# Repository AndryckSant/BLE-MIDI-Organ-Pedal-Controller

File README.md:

# BLE MIDI Organ Pedal Controller

Firmware for an ESP32-based expression-pedal controller that sends MIDI Control Change messages over BLE MIDI. The firmware is organized into application, FSM, service, model, and driver layers.

Firmware version: **1.2.0**

## Features

- BLE MIDI output for two expression pedals and up to eight physical buttons.
- ADS1115 input sampling, pedal smoothing, calibration, normalization, and MIDI mapping.
- Per-pedal adaptive auto-range or manually configured calibration limits.
- Configurable button input polarity and momentary or latch MIDI behavior.
- OLED status display and a Wi-Fi access-point configuration portal.
- System configuration persisted in ESP32 non-volatile storage (NVS), including migration from earlier configuration formats.

## Hardware

- ESP32 with BLE support.
- ADS1115 I2C analog-to-digital converter (default address `0x48`).
- SSD1306 I2C OLED display (default address `0x3C`).
- Up to two expression pedals and eight MIDI buttons.

### Default pin assignments

| Function | ESP32 pin / input |
| --- | --- |
| I2C SDA | GPIO 21 |
| I2C SCL | GPIO 22 |
| Configuration button | GPIO 15 |
| Status LED | GPIO 2 |
| MIDI buttons 1-8 | GPIO 13, 12, 14, 27, 26, 25, 33, 32 |
| Pedal inputs | ADS1115 channels A0 and A1 by default |

Connect the buttons with external pull-down resistors. The dedicated configuration button is also read as a digital input. Connect each pedal output to its assigned ADS1115 input and share ground; use a supply voltage appropriate for the pedal and board.

## Configuration portal

Enter configuration mode by pressing the button on GPIO 15 or sending `c`/`C` through Serial at **115200 baud**. BLE MIDI is stopped while the portal is active.

The ESP32 starts an open Wi-Fi access point named **BLE MIDI Controller Setup**. Connect to it and open the IP address shown on the OLED and in the Serial output. The portal lets you configure:

- Each pedal's enabled state, ADS1115 channel, MIDI channel, MIDI CC, calibration minimum/maximum, and auto-range setting.
- Each button's enabled state, GPIO, input polarity, MIDI channel, MIDI CC, and behavior.
- MIDI channels from 1 to 16 and Control Change numbers from 0 to 127.

Button behavior:

- **Momentary:** sends value 127 when pressed and 0 when released.
- **Latch:** alternates between 127 and 0 on successive presses; release sends nothing. This is the default.

Each button input has a 40 ms debounce interval. Use the assigned MIDI-button GPIOs (13, 12, 14, 27, 26, 25, 33, or 32); GPIO 15 is reserved for configuration mode.

Saving settings or restoring factory defaults persists the configuration to NVS and restarts the device. Sending `x`/`X` exits the portal without saving and returns to normal BLE MIDI operation. If the access point cannot start, the OLED displays an error for five seconds before the device restarts.

Factory defaults enable both pedals on ADS1115 channels A0 and A1, MIDI channel 1, with CC 11 and CC 7 respectively. Adaptive auto-range is enabled. All eight buttons default to disabled, use the GPIO assignments above, and have MIDI channel 1, CCs 20-27, and latch behavior.

## Pedal calibration

Auto-range is enabled by default and adapts the calibration range as new pedal extremes are detected. Disable auto-range to use fixed minimum and maximum values configured in the portal. For a useful fixed calibration, set the minimum below the maximum and exercise the pedal across its intended range.

## Build and upload

1. Install the ESP32 board support and the Arduino libraries required by the source, including Adafruit ADS1X15, Adafruit GFX, Adafruit SSD1306, and the BLE MIDI library.
2. Open `Firmware/main/main.ino` in the Arduino IDE, select the target ESP32 board and port, then compile and upload.
3. Open Serial Monitor at **115200 baud** for startup messages and configuration-mode IP details.
4. Pair the BLE MIDI device named **BLE MIDI Controller** with the host and connect to receive MIDI CC messages.

The web-page source is `Firmware/main/src/core/states/config_page.html`; its firmware-embedded header is `Firmware/main/src/core/states/config_page.h`. After editing the HTML, regenerate the header by running `.\Firmware\tools\embed_config_page.ps1` from the repository root.

## Architecture

- `Firmware/main/main.ino` — Arduino `setup()`/`loop()` wrapper.
- `Firmware/main/src/app/` — application initialization, coordination, and runtime processing.
- `Firmware/main/src/core/` — FSM, event queue, and application states, including BLE, streaming, and configuration.
- `Firmware/main/src/drivers/` — ADS1115, BLE, OLED, and NVS hardware access.
- `Firmware/main/src/models/` — pedal, button, calibration, MIDI, and system configuration data.
- `Firmware/main/src/services/` — configuration persistence, input processing, calibration, display, and MIDI services.
- `Firmware/tools/` — utility for embedding the configuration page in the firmware.
- `Hardware/` — KiCad board design and related hardware files.
- `Docs/` — architecture and configuration-portal notes.

## License

- Firmware and original software in `Firmware/` are licensed under the [MIT License](Firmware/LICENSE).
- Hardware design files in `Hardware/` are licensed under [CERN-OHL-S-2.0](Hardware/LICENSE) (Strongly Reciprocal).
- These licenses apply to the original project work in their respective directories. Third-party libraries and other third-party materials remain under their own licenses; see their respective sources for terms.

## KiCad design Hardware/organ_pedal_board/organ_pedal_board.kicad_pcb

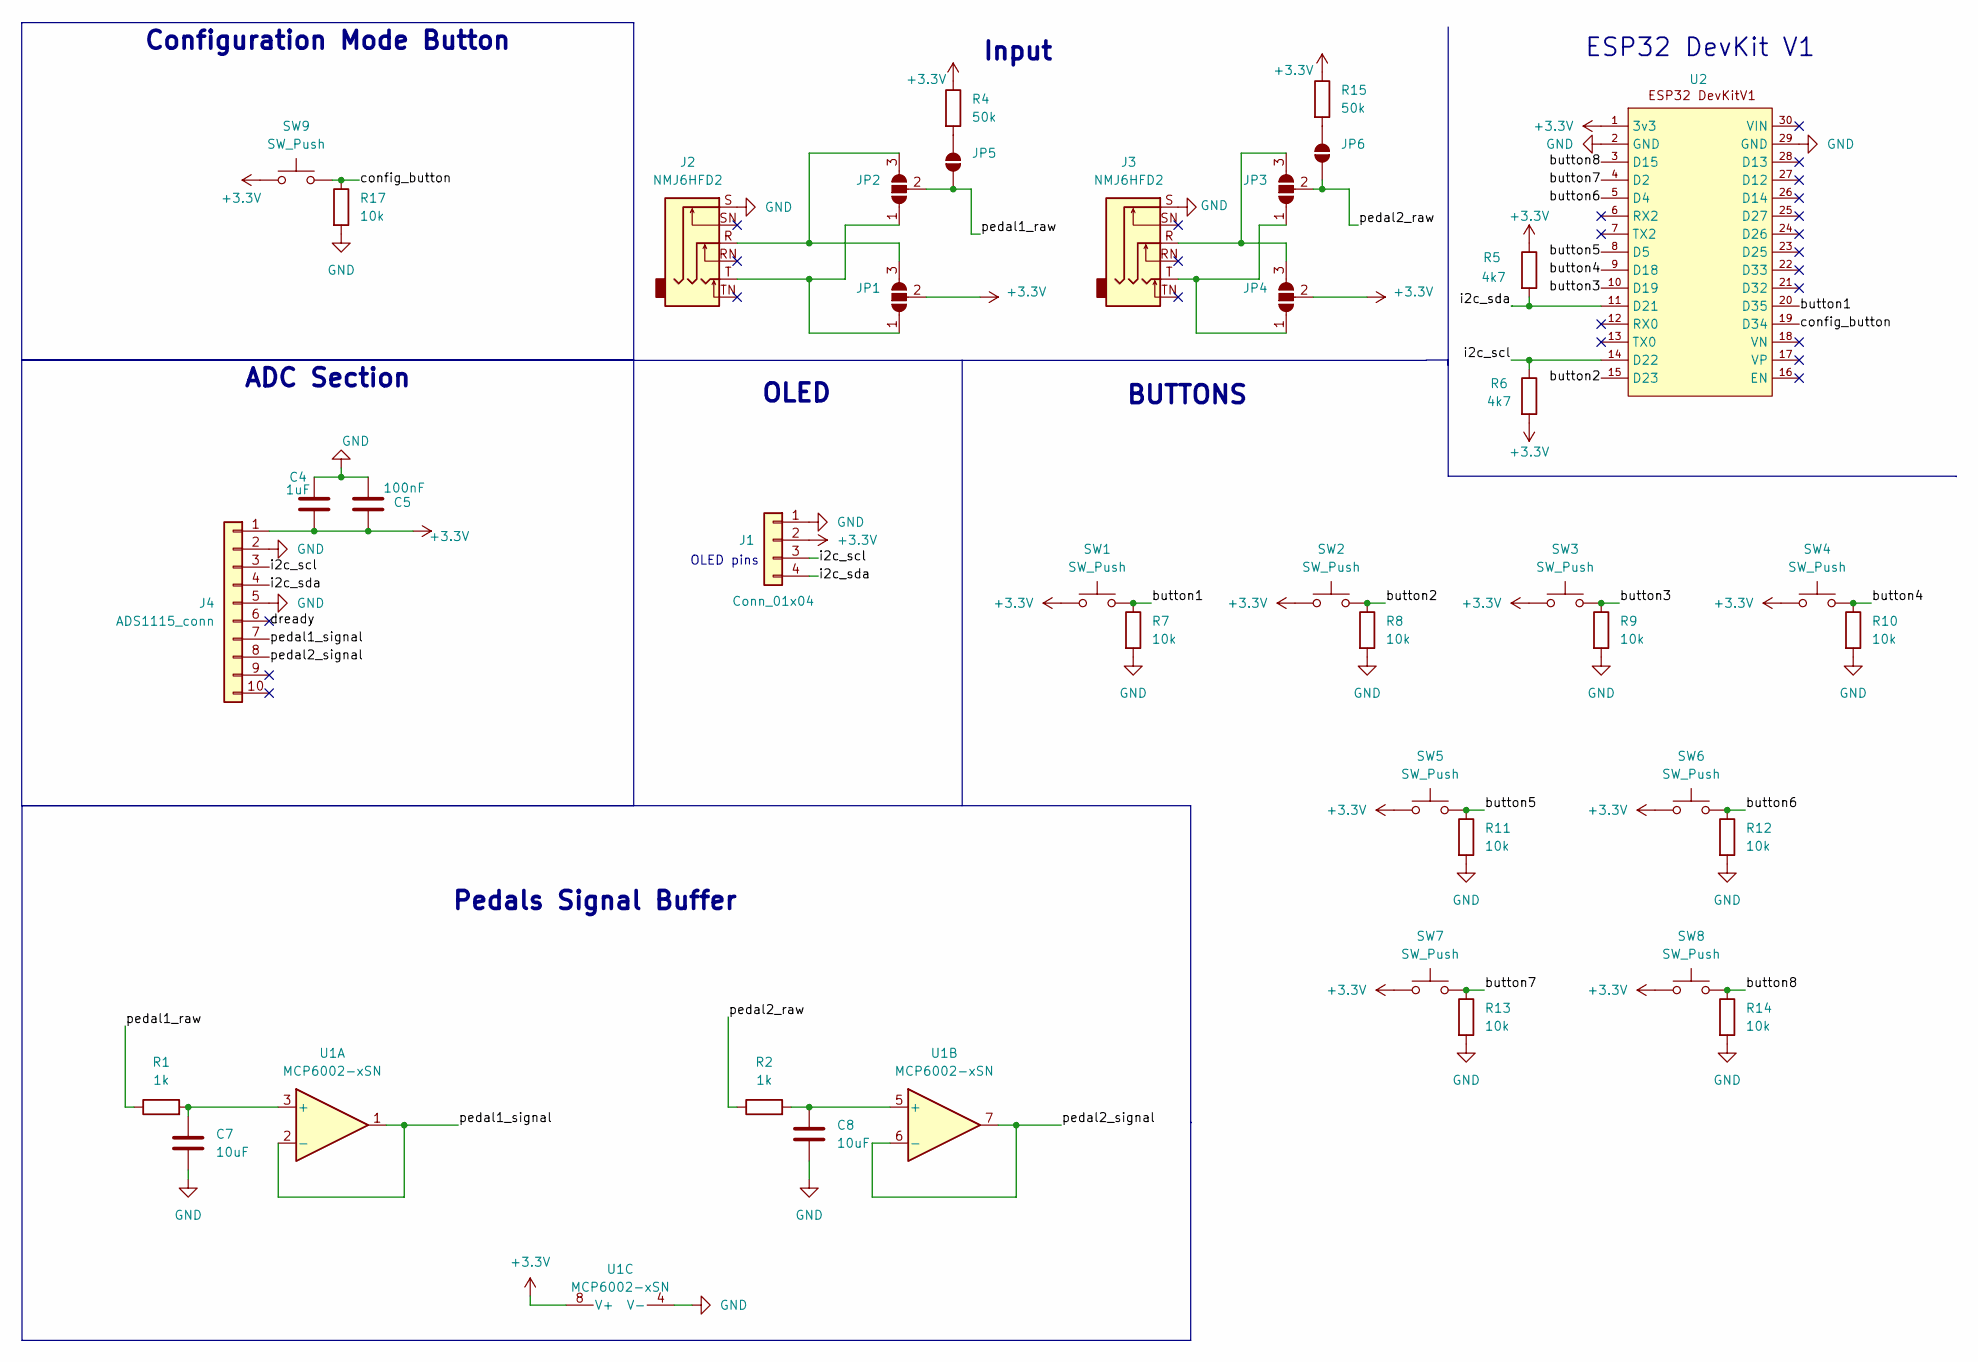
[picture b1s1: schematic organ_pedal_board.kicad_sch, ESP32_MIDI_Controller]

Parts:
C4: 1uF; C_Disc_D3.0mm_W1.6mm_P2.50mm
C5: 100nF; C_Disc_D3.0mm_W1.6mm_P2.50mm
C7, C8: 10uF; C_Disc_D3.0mm_W1.6mm_P2.50mm
J1: Conn_01x04; PinSocket_1x04_P2.54mm_Vertical
J2, J3: NMJ6HFD2; Jack_6.35mm_Neutrik_NMJ6HFD2_Horizontal
J4: ADS1115_conn; PinSocket_1x10_P2.54mm_Vertical
JP1, JP2, JP3, JP4: SolderJumper_3_Open; SolderJumper-3_P1.3mm_Open_RoundedPad1.0x1.5mm
JP5, JP6: SolderJumper_2_Open; SolderJumper-2_P1.3mm_Open_RoundedPad1.0x1.5mm
R1, R2: 1k; R_Axial_DIN0204_L3.6mm_D1.6mm_P1.90mm_Vertical
R4, R15: 50k; R_Axial_DIN0204_L3.6mm_D1.6mm_P1.90mm_Vertical
R5, R6: 4k7; R_Axial_DIN0204_L3.6mm_D1.6mm_P1.90mm_Vertical
R7, R8, R9, R10, R11, R12, R13, R14, R17: 10k; R_Axial_DIN0204_L3.6mm_D1.6mm_P1.90mm_Vertical
SW1, SW2, SW3, SW4, SW5, SW6, SW7, SW8: SW_Push; JST_XH_S2B-XH-A-1_1x02_P2.50mm_Horizontal
SW9: SW_Push; SW_PUSH_6mm
U1: MCP6002-xSN; SOIC-8_3.9x4.9mm_P1.27mm
U2: esp32_devkit_v1_doit

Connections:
+3.3V: C4.2, C5.1, J1.2, J4.1, JP1.2 (C), JP4.2 (C), R4.1, R5.1, R6.2, R15.1, SW1.1, SW2.1, SW3.1, SW4.1, SW5.1, SW6.1, SW7.1, SW8.1, SW9.1, U1.8 (V+), U2.1 (3v3)
/button1: R7.1, SW1.2, U2.20 (D35)
/button2: R8.1, SW2.2, U2.15 (D23)
/button3: R9.1, SW3.2, U2.10 (D19)
/button4: R10.1, SW4.2, U2.9 (D18)
/button5: R11.1, SW5.2, U2.8 (D5)
/button6: R12.1, SW6.2, U2.5 (D4)
/button7: R13.1, SW7.2, U2.4 (D2)
/button8: R14.1, SW8.2, U2.3 (D15)
/config_button: R17.1, SW9.2, U2.19 (D34)
/dready: J4.6
/i2c_scl: J1.3, J4.3, R6.1, U2.14 (D22)
/i2c_sda: J1.4, J4.4, R5.2, U2.11 (D21)
/pedal1_raw: JP2.2 (C), JP5.1 (A), R1.1
/pedal1_signal: J4.7, U1.1, U1.2 (-)
/pedal2_raw: JP3.2 (C), JP6.1 (A), R2.1
/pedal2_signal: J4.8, U1.6 (-), U1.7
GND: C4.1, C5.2, C7.2, C8.2, J1.1, J2.S, J3.S, J4.2, J4.5, R7.2, R8.2, R9.2, R10.2, R11.2, R12.2, R13.2, R14.2, R17.2, U1.4 (V-), U2.2 (GND), U2.29 (GND)
unnamed: J2.T, JP1.1 (A), JP2.1 (A)
unnamed: J2.R, JP1.3 (B), JP2.3 (B)
unnamed: J3.T, JP3.1 (A), JP4.1 (A)
unnamed: J3.R, JP3.3 (B), JP4.3 (B)
unnamed: JP5.2 (B), R4.2
unnamed: JP6.2 (B), R15.2
unnamed: C7.1, R1.2, U1.3 (+)
unnamed: C8.1, R2.2, U1.5 (+)

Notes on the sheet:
ESP32 DevKit V1
BUTTONS
Input
OLED
Pedals Signal Buffer
OLED pins
ADC Section
Configuration Mode Button

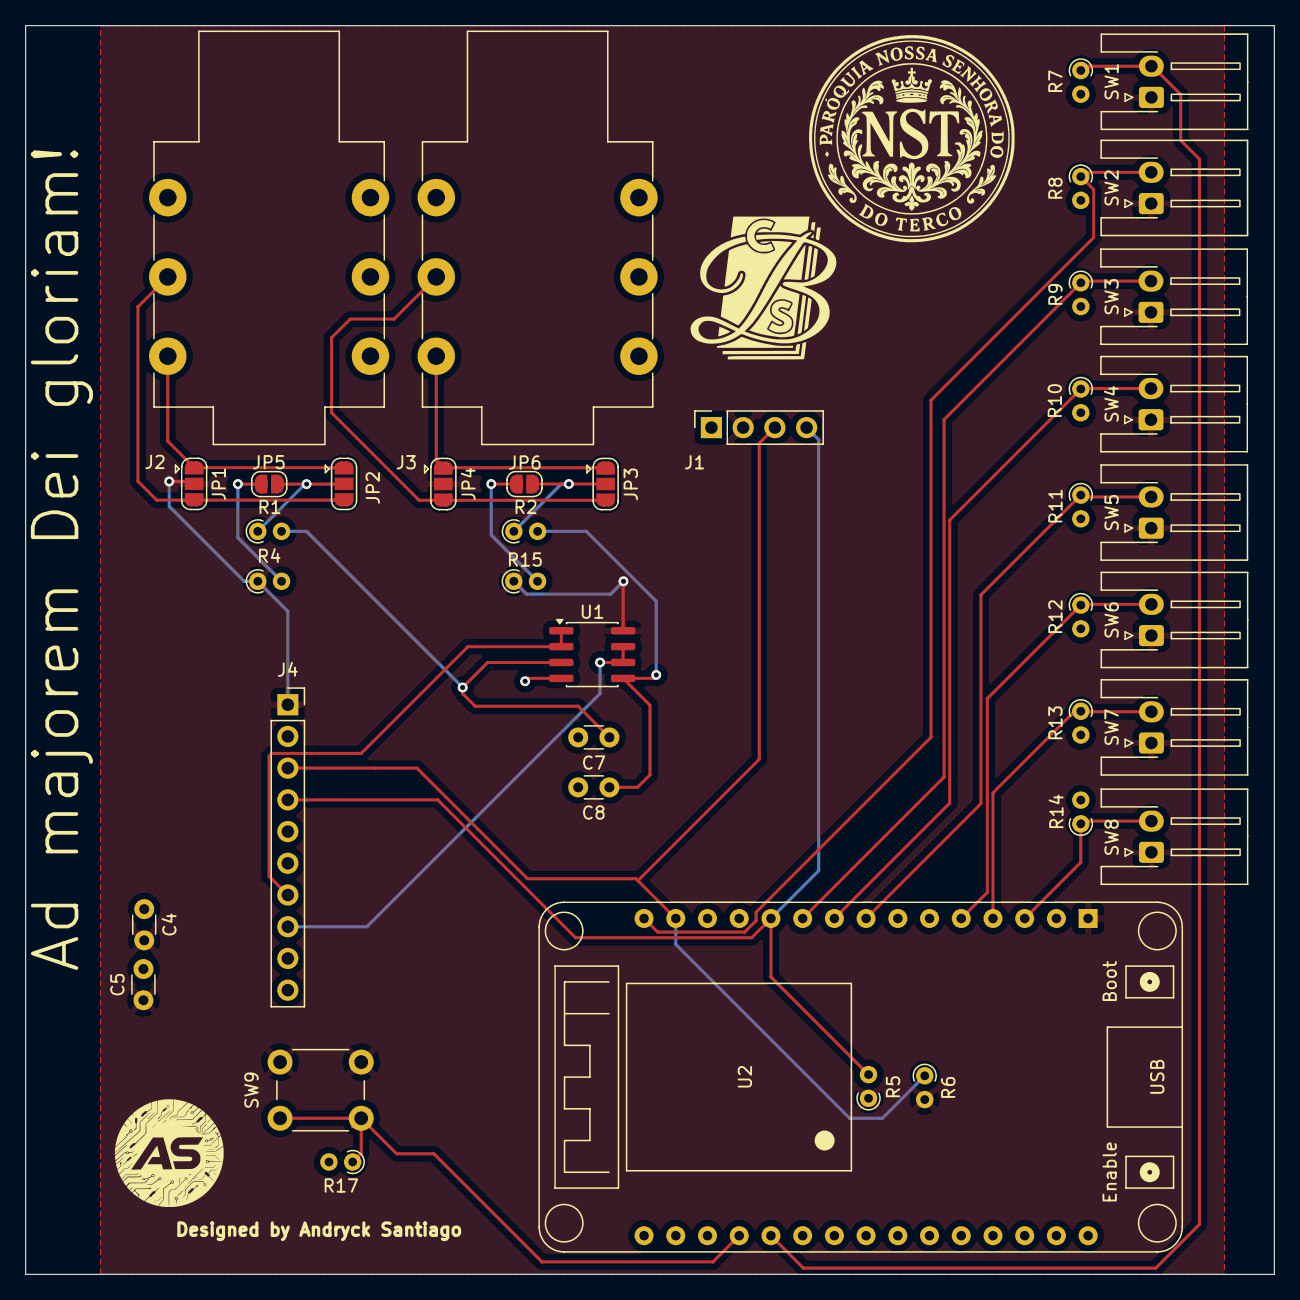
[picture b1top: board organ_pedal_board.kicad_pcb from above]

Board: 2 copper layers, 100.0 x 100.0 mm, 40 parts (0 on the bottom side), 25 nets.

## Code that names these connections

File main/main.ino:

#include <BLEMidi.h>
#include <Arduino.h>
#include <Adafruit_ADS1X15.h>
#include <Wire.h>
#include <Adafruit_GFX.h>
#include <Adafruit_SSD1306.h>


// ===== OLED =====
#define SCREEN_W  128
#define SCREEN_H  32
#define OLED_ADDR 0x3C
Adafruit_SSD1306 oled(SCREEN_W, SCREEN_H, &Wire, -1);
SemaphoreHandle_t i2cMutex;

// ===== HARDWARE CONFIGURATION =====
Adafruit_ADS1115 ads;
const int pedal1_signal = 4;
const int pedal2_signal = 15;
const int i2c_sda = 21;
const int i2c_scl = 22;
const int i2c_dready = 23;

const int SWELL_PEDAL_PIN = 34;
const int LED_STATUS_PIN = 2;  // LED embutido no ESP32
const uint16_t ADC_MAX = 65535;

// ===== MIDI CONFIGURATION =====
const uint8_t SWELL_MIDI_CC = 11;
const uint8_t SWELL_MIDI_CHANNEL = 1;

// ===== BLE CONFIGURATION =====
constexpr char BLE_NAME[] = "Organ Pedal";

// ===== FILTER PARAMETERS =====
constexpr uint8_t DEAD_BAND = 2;
constexpr uint8_t SMOOTH_DIV = 12;
constexpr unsigned long SAMPLE_INTERVAL_MS = 5;
constexpr float CALIBRATION_RATE = 0.001f;  // Taxa de adaptação da calibração

// ===== STATE VARIABLES =====
uint8_t midi_value = 0;
volatile bool isConnected = false;
uint8_t last_value = 255;  // Valor impossível para forçar primeiro envio
int filtered = 0;
unsigned long lastSampleTime = 0;

// ===== CALIBRATION =====
float cal_min = ADC_MAX;
float cal_max = 0.0f;
bool calibrationInitialized = false;

// ===== CALLBACKS BLE =====
// Ajuste: callbacks sem parâmetros (compatível com BLEMidiServer.setOnConnectCallback)
void onConnect() {
  isConnected = true;
  digitalWrite(LED_STATUS_PIN, HIGH);
  Serial.println("BLE Client connected!");
}

void onDisconnect() {
  isConnected = false;
  digitalWrite(LED_STATUS_PIN, LOW);
  Serial.println("BLE Client disconnected.");
}

// ===== PROCESSING FUNCTIONS =====
float organSwellCurve(float x) {
  const float gamma = 0.45f;
  return powf(x, gamma);
}

void sendControlChange(uint8_t channel, uint8_t cc, uint8_t value) {
  if (isConnected) {
    BLEMidiServer.controlChange(channel, cc, value);
  }
}

int readAndFilterSwellPedal(){
  int raw = 0;
  if (xSemaphoreTake(i2cMutex, pdMS_TO_TICKS(20))) {
    raw = ads.readADC_SingleEnded(0);
    xSemaphoreGive(i2cMutex);
  }
  filtered = filtered + (raw - filtered) / SMOOTH_DIV;
  return filtered;
}

void updateCalibration(int value) {
  if (!calibrationInitialized) {
    cal_min = value;
    cal_max = value;
    calibrationInitialized = true;
    return;
  }
  
  if (value < cal_min) {
    cal_min = cal_min * 0.9f + value * 0.1f; 
  } else {
    cal_min = cal_min * (1.0f - CALIBRATION_RATE) + value * CALIBRATION_RATE;  
  }
  
  if (value > cal_max) {
    cal_max = cal_max * 0.9f + value * 0.1f; 
  } else {
    cal_max = cal_max * (1.0f - CALIBRATION_RATE) + value * CALIBRATION_RATE;  
  }
}

// ===== CORE 0: OLED STATUS =====
void taskOLED(void* param) {
  // Inicializa OLED
  if (xSemaphoreTake(i2cMutex, portMAX_DELAY)) {
    oled.begin(SSD1306_SWITCHCAPVCC, OLED_ADDR);
    oled.clearDisplay();
    oled.display();
    xSemaphoreGive(i2cMutex);
  }

  for (;;) {
    if (xSemaphoreTake(i2cMutex, pdMS_TO_TICKS(30))) {
      oled.clearDisplay();
      oled.setTextColor(SSD1306_WHITE);
      oled.setTextSize(1);

      // Faixa amarela (Y 0-15): cabeçalho
      oled.setCursor(0, 4);
      oled.print(BLE_NAME);

      // Faixa azul (Y 16+): conteúdo
      oled.setCursor(0, 18);
      oled.print("BLE: ");
      oled.print(isConnected ? "Conectado" : "Aguardando...");

      oled.setCursor(0, 30);
      oled.printf("CC%d: %d", SWELL_MIDI_CC, midi_value);

      oled.setCursor(0, 42);
      oled.printf("Cal: %.0f - %.0f", cal_min, cal_max);

      // Barra de expressão
      oled.drawRect(0, 54, 128, 10, SSD1306_WHITE);
      int barW = map(midi_value, 0, 127, 0, 126);
      oled.fillRect(1, 55, barW, 8, SSD1306_WHITE);

      oled.display();
      xSemaphoreGive(i2cMutex);
    }

    vTaskDelay(pdMS_TO_TICKS(100)); // ~10 FPS
  }
}

void setup() {
  Serial.begin(115200);
  Serial.println("Starting BLE MIDI Device");

  // Mutex I2C (compartilhado OLED + ADS1115)
  i2cMutex = xSemaphoreCreateMutex();

  BLEMidiServer.begin(BLE_NAME);
  BLEMidiServer.enableDebugging();
  BLEMidiServer.setOnConnectCallback(onConnect);
  BLEMidiServer.setOnDisconnectCallback(onDisconnect);
  
  // Configurações do hardware
  pinMode(LED_STATUS_PIN, OUTPUT);
  digitalWrite(LED_STATUS_PIN, LOW);

  Wire.begin(i2c_sda, i2c_scl);
  delay(100);
  // Configura ADC
  ads.setGain(GAIN_ONE);

  //Diagnóstico de localização de dispositivos...
  for (uint8_t addr = 1; addr < 127; addr++) {
    Wire.beginTransmission(addr);
    if (Wire.endTransmission() == 0) {
      Serial.printf("Found device at 0x%02X\n", addr);
    }
  }
  if(!ads.begin()){
    Serial.println("ADS1115 not found!");
    while (1);
  }
  delay(100);
  
  // Pisca LED para indicar que está pronto
  for (int i = 0; i < 3; i++) {
    digitalWrite(LED_STATUS_PIN, HIGH);
    delay(250);
    digitalWrite(LED_STATUS_PIN, LOW);
    delay(250);
  }

  // Lança task OLED no Core 0
  xTaskCreatePinnedToCore(taskOLED, "OLED", 4096, NULL, 1, NULL, 0);
  
  Serial.println("waiting for connections...");
}

void loop() {

  unsigned long currentTime = millis();
  if (currentTime - lastSampleTime < SAMPLE_INTERVAL_MS) {
    delay(1); // permite tarefas do sistema/BLE
    return;
  }
  lastSampleTime = currentTime;
  
  
  if (isConnected) {
    int swellFilteredValue = readAndFilterSwellPedal();
    updateCalibration(swellFilteredValue);
    
    
    float span = cal_max - cal_min;
    if (span < 10.0f) span = 10.0f;  
    
    
    float normalized = constrain((swellFilteredValue - cal_min) / span, 0.0f, 1.0f);
    
    
    float curved = organSwellCurve(normalized);
    

    midi_value = (uint8_t)(curved * 127.0f);
    
    if (abs((int)midi_value - (int)last_value) > DEAD_BAND) {
      Serial.printf("MIDI CC%d: %d (raw: %d, cal: %.0f-%.0f)\n", 
                    SWELL_MIDI_CC, midi_value, swellFilteredValue, cal_min, cal_max);
      sendControlChange(SWELL_MIDI_CHANNEL, SWELL_MIDI_CC, midi_value);
      last_value = midi_value;
    }
  }
  
  
}

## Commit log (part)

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2025-11-22 Add README.md for Expression Pedal BLE MIDI project
2025-11-22 Initial commit of BLE MIDI controller code
2025-11-22 Add .gitignore to exclude organ_pedal_board-backups directory
2025-11-23 Refactor: swell pedal handling, improve calibration logic and applied logarithmic curve to pedal reading.
2025-11-23 PCB and board schematic files
2025-11-23 Docs: Update README.md to enhance project description and usage instructions for BLE MIDI Organ Pedal Controller
2025-11-23 Add resistor R2 to the schematic at (171.45, 106.68)
    - Introduced a new resistor component (R2) with a value of 100 ohms.
    - Added a junction point to connect the resistor within the circuit.
    - Updated properties for the resistor including reference, value, and datasheet.
2026-02-05 Refactor: Enhance BLE connection handling and improve swell pedal calibration logic
2026-02-05 Refactor: Update KiCad project files for improved visibility and settings
2026-02-05 Implement feature X to enhance user experience and optimize performance
2026-02-05 Refactor: Update BLE connection callbacks and enhance hardware configuration for improved functionality and added ADS1115 support
2026-02-05 Refactor code structure for improved readability and maintainability
2026-02-05 Implement feature X to enhance user experience and fix bug Y in module Z
2026-02-05 Implement initial structure for code changes
2026-02-06 Add text annotations and adjust component positions in schematic
2026-02-12 Feat
2026-02-26 Fix wire and label positions in schematic for improved clarity
2026-02-26 Refactor: improved readability and maintainability
2026-02-26 Feat: add OLED display functionality and I2C mutex for thread safety
2026-02-27 Feat: added OLED circuit to board schematics
2026-02-28 Feat: added 8 buttons and finished schematics.
2026-03-05 Update active layer and pad dimensions in organ pedal board design
    - Changed active layer from 25 to 5 in the project settings.
    - Updated pad drill size from 0.8 to 2.0, height from 1.27 to 4.0, and width from 2.54 to 4.0 for improved component compatibility.
2026-04-10 Fix: update OLED height to 32 and set MIDI channel to 1
2026-04-11 Fix: Corrected MCP6002 power supply, corrected P10 plug 1 MCP6002 signal output
2026-04-11 Fix: Corrected vias and esp32 pin assignment
2026-04-11 Fix: Component placement enhancement
2026-04-11 Add: First PCB of organ pedal board schematic
2026-04-11 Refactor: code structure for improved readability and maintainability
2026-04-23 Refactor: enhance pedal 2 handling and calibration logic
2026-04-30 Refactor: Pedal Plug circuit
